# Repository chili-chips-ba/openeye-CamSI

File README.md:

# openEye-CamSI
Also see our [openEye-CamSI-Ethernet](https://github.com/chili-chips-ba/openeye-CamSI-ethernet) repo.

## Objective I

### Upgrade openCam Performance and Functionality
The goals of this development are to deliver complete video pipeline for three popular hi-rez imaging/camera sensors:
 - `2-lane RPiV2.1`, based on Sony IMX219, in `1280x720P@60Hz` RGB888 - `HD`
 - `4-lane OneInchEye`, based on Sony IMX283, in `1920x1080P@60Hz` RGB888 - `FHD`
 - `2-lane OV2740`, in a "Webcam" setup for Lukas Henkel's [openLaptop](https://resources.altium.com/p/open-source-laptop-part-one)

This is for mature, low-cost **Artix7 FPGAs**, by using its **IBUFDS, IDELAY, ISERDES** primitives in the camera front-end. These primitives are available in all IOBs, hence ubiquitous, relatively easy to work with, and already supported by opensource PNR for Xilinx Series7. This also allows future reduction of the total solution cost by migrating to [Spartan7](https://www.xilinx.com/video/fpga/spartan-7-technical-overview.html?_ga=2.252819658.271111311.1715447274-1421952438.1715447272), which does not have GTP transceivers (aka "true SerDes").

>To be clear -- We don't plan on using any of the 3rd party D-PHY front-end silicon devices specified in [XAPP894](https://github.com/chili-chips-ba/openeye-CamSI/blob/main/0.doc/Xilinx/MIPI/xapp894-d-phy-solutions.pdf). Moreover, we won't even use the passive signal conditioning networks that Xilinx is recommending. Instead, our objective is to achieve robust *Signal Integrity* (SI) and flawless HD/FHD video flow by pulling-in only on-chip resources.

This brings about multiple challenges. Compared to [StereoNinja's](https://github.com/StereoNinja/StereoNinjaFPGA) original work, which was for LatticeSemi ECP5 FPGA, our target device does not come with D-PHY receiver circuit *(no wonder why Artix7 costs less* :innocent:*)*.

On top of it, we are doing it on meager internal-to-FPGA BRAM budget, without expending much storage. In other words, PSRAM, SDRAM, DDR or similar external chips are NOT called to rescue. That's a major upgrade to StereoNinja's design, who realized end-to-end, camera-to-monitor streaming for only 640x480 VGA, and only in Grayscale, far below our vibrant RG888 color palette and HD/FHD quality. 

>This design is simpler and more affordable, hence uniquely appealing to the makers. It also paves a path to a cost-efficient openLaptop camera subsystem.

It is indeed the NLnet's objective for this project to bring StereoNinja's pioneering work to an order of magnitude higher performance and functionality level.

On the video feed sink side, we plan to showcase real-time streaming to:
 - **HDMI** monitor
 - **1Gbps Ethernet**, using UDP packets, rendered on a PC with [VLC Player](https://www.videolan.org)

The follow on "Webcam" project (aka Phase2) is to add **UVC** (USB2.0 Video Class) to this list. In prep for this future work, we plan to develop a number of add-on functions:
 - `Enable OV2740 camera chip`
 - `Image Signal Processing (ISP) 4 Webcam`
    > White Balance, Color Correction, Gamma Correction
 - `Video Compression 4 Webcam` - JPEG
    > Not needed for 1GE. But, compression is a must-have for the 1024P@30Hz over USB2

While our design is pushing Artix7 to its limits, it's these very silicon limits that stand in the way of getting more from the given imaging sensors. Recall that even StereoNinja's generally faster and better LatticeSemi FPGA cannot generate HDMI at 1920x1080@60Hz. 

Using Vivado tool chain, we were able to bring this design to the point where the only remaining factor preventing further resolution increase is the *Max Specified Toggle Rate* for Artix7 I/O structures and clock distribution networks.

## Objective II
### Add to opensource ecosystem 4 Xilinx

We are thrilled to use [openXC7](https://github.com/openXC7) toolkit, including its web-based CI/CD flow. That's both for the security of images taken, and to help openXC7 attain the level of robustness found in commercial / proprietary CAE tools, Xilinx Vivado in particular. In that sense, OpenEye-CamSI is the continuation of our [TetriSaraj](https://github.com/chili-chips-ba/openXC7-TetriSaraj), which was the first openXC7 test case for a design more complex than a mere blinky. 

>Our goal is to bring to the light issues that arrive from openXC7's first-ever exposure to demanding, cutting-edge designs like this one. 

It is important to note that, in its current state, openXC7 is rather immature, without even the basic timing awareness, yet alone timing-driven optimizations. It has never been used for designs that push the underlying silicon to the max. The as-is openXC7 is simply not adequate for proper timing closure.

While another project is underway and looking to plug this major opensource STA gap, it won't be ready for our Phase1. We're therefore planning Phase2 and Phase3, hoping to try this new timing closure prowess... Stress-testing, congesting, overwhelming it, all for the sake of making it more amenable to realizing higher Utilization and Fmax metrics with silicon at hand. 

The choice of our development platform was governed by the benefit for the greater community. The boards were selected for their opensource [CRUVI](https://github.com/micro-FPGA/CRUVI/blob/master/docs/CRUVI_Specification.pdf) connectivity spec. Yes, they are hardly used and don't come with support collateral found on the more popular hardware platforms. That's exactly why we opted for them!

We have indeed come across quite a few board problems and idiosyncrasies, spending a fair amount of time chasing issues that simply should not have been there. Still, since those are both opensource and EU products, this extra effort was for a good cause. We are certain that this project will help increase their visibility, and boost their acceptance rate among open makers. 

## Execution Play 1
### Laying a foundation
- [x] ✔ Familiarize with [Trenz](https://github.com/chili-chips-ba/openeye-CamSI/tree/main/0.doc/Trenz) hardware platform: Connectivity, clocking, power, etc. 
- [x] ✔ Bring up Blinky on Trenz
>___
- [x] ✔ Standalone HDMI image generation: 1280x720P@60Hz  RGB888 (HD)
- [x] ✔ Standalone HDMI image generation: 1920x1080P@30Hz RGB888 (FHD@30Hz)
- [x] ✔ Standalone HDMI image generation: 1920x1080P@60Hz RGB888 (FHD@60Hz). Established that FHD@60Hz is physically impossible with given silicon
>___
- [x] ✔ Experiments with IMX219 configuration and resolution options
- [x] ✔ Sniff Raspberry Pie interactions with Camera
- [x] ✔ Familiarize with *libcamera* drivers
>___  
- [x] ✔ Experiments with LVDS and termination schemes.
      How to do better than XAPP894, sharing insights with Lukas
>___
- [x] ✔ Test opensource [4-lane adapter](https://github.com/chili-chips-ba/openeye-CamSI/tree/main/0.doc/CRUVI-camera-adapter), sharing feedback with Edmund
- [x] ✔ Full redesign, fixing [bugs](https://github.com/chili-chips-ba/openeye-CamSI/blob/main/0.doc/CRUVI-camera-adapter/Technical-Note.TN-mipi.REV1.pdf) and expanding scope, to now include 2 and 4 lanes
>___
- [x] ✔ Clock Detection logic without standard LP I/O
- [x] ✔ SYNC Decoding logic and Byte Alignement
- [x] ✔ Word Alignement
- [x] ✔ Header Decoding and Stripping
- [x] ✔ Acquire static image from Camera, transfer it to DualPort BRAM, then HDMI
>___
- [x] ✔ Uncovered & debugged crosstalk problems on VHDPlus CRUVI adapter
- [x] ✔ Found Trenz [signal inversions and inconsistencies](https://github.com/chili-chips-ba/openeye-CamSI/blob/main/0.doc/CRUVI-camera-adapter/CRUVI-Pinout-4-and-2-lanes.xlsx), then shared with Antti
>___
- [x] ✔ HD video transfer from Camera to HDMI - At first jerky, with visible frame loss
- [x] ✔ Found CDC bug in opensource AsyncFIFO, sharing insights with IP owners
>___
- [x] ✔ Debayering logic for Color Space Conversion     
- [x] ✔ Synchronization logic for smooth video streaming, w/o external storage
>___

For this first play, the hardware was used in the following config:
- Trenz Carrier Card (TEB0707-02)
- Trenz 4x5 SoM with Artix-7 FPGA (TE0711-01)
- VHDPlus HDMI + 2-lane CSI Camera adapter
- Raspberry Pi V2.1 camera (Sony IMX219)

#### *Standalone HDMI image generation*
Our HDMI [image generator](https://github.com/chili-chips-ba/openeye-CamSI/tree/main/1.hw/lib/ip/hdmi) is limited by the toggle rate that's realistically possible with Artix7 clock and I/O primitives. The max we can get from it is:
- 720P@60Hz
- 1080P@30Hz
  
More about this and silicon limitations in [HDMI issue](https://github.com/chili-chips-ba/openeye-CamSI/issues/1#issue-2278453405). Here is the test image that our HDMI RTL outputs on its own, w/o camera connected to it:

#### *I2C for Camera Configuration*
There are many configurable registers in the IMX219 imaging sensor. Having fully familiarized with them, both by sniffing RPi I2C transactions and running own experiments, we've settled on the 720P@60Hz. I2C Controller was developped from the scratch, and used to load camera registers. More on it in [I2C issue](https://github.com/chili-chips-ba/openeye-CamSI/issues/3). 

Here is an illustration of I2C waveforms, i.e. our Control Plane protocol.

#### *Camera Connection*
Sony [IMX219](0.doc/Sensor.2-lane.RPi2.1/IMX219PQ.Datasheet.pdf) camera sensor is used for image acquisition. It is connected to FPGA with a 15-pin flex cable (FFC), using [VHDPlus](https://vhdplus.com/docs/components/camera) CRUVI module. We recommend checking our [blog](https://www.chili-chips.xyz/blog/untwisting-rpi5-camera-connectivity) for additional detail on this topic.

It turned out that the 4-lane CRUVI connector had a serious design flaw, essentially shorting system power. Having identified its root cause, we had to fully redesign it. We have also run into Trenz I2C wiring and supply complications related to onboard CPLD. Luckily, we managed to find a way around it without having to open the CPLD and change its internals.

#### *High-speed Signaling and Signal Integrity*
The VHDPlus CRUVI carries three 100 Ohm termination resistors, one for clock, plus two for data, as shown below: 

Location of these resistors close to data source is a major SI problem. Termination must be placed at the end of *Transmission Line* (TL), next to sink. Yet, on this system, the termination is not only misplaced, but there are also three connectors in the path of high speed signals:
- Camera to CRUVI -> `that's where the stock termination is placed`
- CRUVI to Carrier Card
- Carrier to FPGA SOM Card.

Consequently, we had to remove the stock termination and replace it with internal-to-FPGA resistors, so essentially relocating it to the very end of TL.

When Artix7 internal termination is used in connecton to LVDS_25 IOSTANDARD, it is important to set the correspoding bank's VCCIO to 2.5V. Only then will their differential resistance be 100 Ohms. 

That's on Trenz hardware done in the following way:
- switch DIP 2 to ON state, to set the IOV to 2.5V
- use Jumpers J14, J16, and J17 to connect VCCIO to IOV.
  
#### *Detection of Camera Clock Activity Intervals*
Once all these hardware and board problems were put behind, we turned focus back to RTL design. 

Given the goal to minimize overhead and eliminate the need for LP pins (see XAPP894), RTL had to provide a clever substitute for our non-existent I/O compared to standard Camera Serial Interface. After some experimentation, we settled on a scheme that detects blanking intervals between frames by using *Clock_Lock_FSM* with thresholds and timeouts. The output of this *Clock_Lock_FSM* is then used as global reset for the camera side of pipeline. That's to say that the video pipeline is out of reset only when camera clock is active and stable.

#### *CDC and Video Synchronization*
To have fluid and seamless video, we need to pass Pixel data with Line and Frame synchronization pulses from Camera to HDMI clock. Aiming for low-cost solution, this *Clock Domain Crossing* (CDC) and *Timebase Handoffs* are accomplished using Line Buffering instead of full Frame Buffering, so saving storage resources. More on this topic in [Line buffering issue](https://github.com/chili-chips-ba/openeye-CamSI/issues/2).

In addition to AsyncFIFO for **csi_clock->hdmi_clock** CDC, the signals that play crucial role in the *Timebase Handoffs* process are:
- csi_line_in
- hdmi_line_in

They mark the beginning of each new scan line in incoming video from Camera, as well as outgoing line to HDMI.

Furthermore, Async FIFO is kept in reset when either Camera or HDMI are Out-Of-Frame. It is through this **fifo_areset_n** and **hdmi_reset_n** that we are forcing HDMI to track the Camera. **rgb2hdmi** is the bridge between Camera and HDMI+GE worlds. Timing diagram below contains additional detail.

In all honesty, it took us a bit of trial-and-error to get it right. That was to some extent due to CDC bug we found in the fullness count of AsyncFIFO, which is the IP block we pulled from one of the opensource libraries. 

In the end, when everything was tuned, and AsyncFIFO CDC problem factored out of the solution, the final result came to be as nice and polished as follows:

#### *Clock and Block Diagram*

The following diagram illustrates design clocking scheme and block structure:

Design operates off of a single **external 100MHz** clock, from which we generate **200MHz refclk** for IDELAY and detection of camera activity. The camera clock comes in two forms:
- **CSI Bit** clock, for sampling and capturing incoming DDR data
- **CSI Byte** clock (= Bit clock / 4) for the rest of CSI video pipeline

The frequency of camera *Bit* and *Byte* clocks is the function of sensor resolution. A PLL on HDMI side generates two specific clocks from the common 100MHz input:
- **Parallel**, for RGB888 HDMI data
- **Serial**, (x5) for OSERDES and transmission of multiplexed video to monitor

The frequency of these two clocks is the function of HDMI resolution. We provide Verilog macros in the central *`top_pkg.sv`* for selection of HDMI resolution. 

The datapath is a straight video pipeline with option for width scaling via `NUM_LANE` parameter, which is also located in the central *top_pkg.sv*. 

The pipeline starts with circuits for capturing serial *Double Data Rate* (DDR) camera stream, eye-centering it using IDELAY, converting it to paralell format with ISERDES, then searching for *Byte boundaries*, followed by *Word alignement*, followed by *Packet Header* parsing and extraction of video *Payload* pixels.

It is only at this point, where video is *unpacked*, that we may engage in ISP. The ISP is a set of functions that could be as elaborate as one is willing to invest in them. Here is a [good read on it](https://www.eecs.yorku.ca/~mbrown/ICCV19_Tutorial_MSBrown.pdf). The extent of ISP for this project is clearly defined. The future Phase2 and Phase3 would add more. 

*Debayer* is the first ISP function we implemented. Without it, the displayed colors would have looked weird. More on it in [Debayer issue](https://github.com/chili-chips-ba/openeye-CamSI/issues/4).

## Execution Play 2
### Widening up the pathway
- [x] ✔ Repeat the same for the 4-lane IMX283 camera sensor
- [x] ✔ Step-by-step introduce the following 3 ISP elements:
  - [x] ✔ Debayer
  - [x] ✔ Dead Pixel Management
  - [x] ✔ Manual Exposure Control 
- [x] ✔ Implement another (lower) resolution of our choice

### *IMX283 Sensor Configuration for Different Resolutions*

Configuring the IMX283 sensor for different resolutions requires precise adjustment of its registers. For each data entry, the first four digits represent the register address, while the last two digits indicate the value to be written. Below, we describe the configuration process for achieving both **720p** and **1080p** resolutions at 60 FPS using **Mode 3** and **Mode 2**, respectively.

This sensor requires specific delays after setting some registers. In the [.mem](https://github.com/chili-chips-ba/openeye-CamSI/tree/main/1.hw/lib/ip/i2c_master) files, this is implemented as an additional byte appended to the three bytes representing the address and value of each register. These delays are crucial for ensuring proper operation and stability of the camera. More details can be found in our [issue](https://github.com/chili-chips-ba/openeye-CamSI/issues/29).

### **720p Resolution (60 FPS)**

For 720p resolution, **Mode 3** is used, which applies **3x3 horizontal/vertical binning**. This method combines pixel values within a 3x3 grid for each raw color channel, reducing resolution while maintaining image quality.

#### *Mode Settings*
The following registers enable **Mode 3** operation:
- `3004 1e`
- `3005 18`
- `3006 10`
- `3007 00`

#### *Frame Dimensions*
- **Y_OUT_SIZE**: Set the vertical size to 722 (0x2D2) to account for skipping 2 rows for debayer processing:
  - `302f d2`
  - `3030 02`
- **WRITE_VSIZE**: Set the vertical output size to 726 (0x2D6):
  - `3031 d6`
  - `3032 02`

#### *Frame Cropping*
- **H_TRIMMING_START**: Start the horizontal cropping at position 840 (0x348):
  - `3058 48`
  - `3059 03`
- **H_TRIMMING_END**: End the horizontal cropping at position 4584 (0x11E8):
  - `305a e8`
  - `305b 11`

These settings result in **1920 8-bit data points per line**, equivalent to **1280 12-bit raw data points** used for color processing.

#### *Timing Configuration for 60 FPS*
- **VMAX**: Set to 2551 (0x9F7) to ensure frame blanking:
  - `3038 f7`
  - `3039 09`
- **HMAX**: Set to 470 (0x1D6) to ensure line blanking:
  - `3036 d6`
  - `3037 01`

These settings ensure a frame rate of **60 FPS**.

### **1080p Resolution (60 FPS)**

For 1080p resolution, **Mode 2** is used, which applies **2x2 horizontal/vertical binning**. This method combines pixel values within a 2x2 grid for each raw color channel, maintaining higher resolution while reducing the overall pixel count.

#### *Mode Settings*
The following registers enable **Mode 2** operation:
- `3004 0d`
- `3005 11`
- `3006 50`
- `3007 00`

#### *Frame Dimensions*
- **Y_OUT_SIZE**: Set the vertical size to 1082 (0x43A):
  - `302f 3a`
  - `3030 04`

#### *Frame Cropping*
- **H_TRIMMING_START**: Start the horizontal cropping at position 840 (0x348):
  - `3058 48`
  - `3059 03`
- **H_TRIMMING_END**: End the horizontal cropping at position 4584 (0x11E8):
  - `305a e8`
  - `305b 11`

These settings result in **2880 8-bit data points per line**, equivalent to **1920 12-bit raw data points** used for color processing.

#### *Timing Configuration for 60 FPS*
- **VMAX**: Set to 2234 (0x8BA) to ensure frame blanking:
  - `3038 ba`
  - `3039 08`
- **HMAX**: Set to 540 (0x21C) to ensure line blanking:
  - `3036 1c`
  - `3037 02`

These settings ensure a frame rate of **60 FPS**.

### **Comparison of Configurations**

| Resolution | Mode   | Binning | Y_OUT_SIZE | VMAX   | HMAX | Frame Rate |
|------------|--------|---------|------------|--------|------|------------|
| 720p       | Mode 3 | 3x3     | 722        | 2551   | 470  | 60 FPS     |
| 1080p      | Mode 2 | 2x2     | 1082       | 2234   | 540  | 60 FPS     |

These configurations leverage the IMX283's advanced binning capabilities to optimize performance while maintaining high image quality.

You can watch a demonstration of this setup in action at the following link:

#### *Dead Pixel Management*

One of the key challenges in working with high-resolution sensors, like the IMX283, is managing dead pixels. These are defective pixels on the sensor that can negatively impact image quality. On this system, several strategies were implemented to effectively eliminate the impact of dead pixels.

#### *Resolution Constraints and the Use of Binning*

Due to the limitations of the Artix-7 FPGA, it is not possible to support the full resolution output of the IMX283 sensor. To address this, the resolution was reduced while still preserving image quality by utilizing all available pixels on the sensor. This was achieved through **binning**, a preprocessing step offered by the sensor itself.

- **For 720p Resolution**:  
  A **3x3 binning** method is used. From an 8x8 matrix of pixels, a 2x2 matrix is generated. This means that each new pixel is a combination of several neighboring pixels.
  
- **For 1080p Resolution**:  
  A **2x2 binning** method is used. From a 4x4 matrix of pixels, a 2x2 matrix is generated, combining adjacent pixels into one.

This process is illustrated in the image below:

By combining neighboring pixels, binning effectively acts as a form of filtering. This directly mitigates the effect of dead pixels, as their contribution is averaged out with surrounding pixel data.

#### *Debayering and Additional Averaging*

In addition to binning, the **debayering algorithm** implemented on this system further reduces the impact of dead pixels. The algorithm performs additional averaging across pixels to reconstruct color information. This further minimizes the possibility of dead pixels appearing in the final image.

#### *Manual Exposure Control*

Manual exposure control in the IMX283 sensor is achieved through the configuration of the `SVR` (Start Vertical Readout) and `SHR` (Start Horizontal Readout) registers. These registers determine the timing of the sensor's integration period, which is critical for controlling exposure and image brightness.

In our configuration we use:
1. **SVR = 0**: This value sets the integration start vertical period to the minimum possible value, effectively aligning the start of integration with the beginning of the readout period.
2. **SHR = 16**: This value specifies the integration start horizontal period. A higher `SHR` value reduces the integration time by shifting the horizontal readout window closer to the end of the frame.

By selecting these values, the integration time is minimized, which is suitable for scenarios with bright lighting conditions or high frame rate requirements.

## Execution Play 3 - Ethernet streaming
- [x] ✔ Add 1GE as second video sink, then move display to remote PC, via UDP VLC
- [x] ✔ Document implementation via block diagram and project repo

For additional detail, see our [openEye/CamSI-Ethernet](https://github.com/chili-chips-ba/openeye-CamSI-ethernet) repo.

## Execution Play 4 - Porting to openXC7
- [x] ✔ Create snap-free installation workflow
- [x] ✔ Port final design from Vivado to openXC7
- [x] ✔ Simulate it with Verilator and cocoTB, in CI/CD system  
- [x] ✔ Document scripts and flows used in this process

This task validates our Vivado-proven RTL with the openXC7 toolchain for Xilinx Series7 devices. The objectives are:
 - identify limitations in the opensource synthesis and PnR flow
 - document and analyze them
 - then collaborate with the openXC7 team to find the root causes and drive to resolutions.

#### openXC7 installation without Snap

A complete local installation method is provided for setting up the **openXC7 FPGA toolchain** without relying on Snap packages. This approach ensures full control over the environment and avoids Snap-related system constraints.

➡️ Full documentation: [Installation Guide](https://github.com/chili-chips-ba/openeye-CamSI/blob/main/3.build/openXC7/README.md)

#### Resolved Issues

Our extensive testing has resulted in uncovering a multitude of problems. They are fully documented and tracked in the relevant [openXC7 issues](https://github.com/chili-chips-ba/openeye-CamSI/issues?q=is%3Aissue%20label%3AopenXC7), along with specific testcase and solution we've arrived to with openXC7 developers.

#### Remaining Challenge: OSERDES10 Support

One significant limitation remains: openXC7 currently supports only single OSERDES configurations with maximum 8-to-1 muxing ratio. Our design requires 10-to-1 serialization using Master-Slave OSERDES setup (two cascaded OSERDES), which is yet to be supported. As the openXC7 team continues working on this advanced use case, our [Issue42](https://github.com/chili-chips-ba/openeye-CamSI/issues/42) remains open for tracking purposes.

#### Bonus Deliverable: SoftOSERDES10 workaround for Issue42

Looking to temporarily alleviate OSERDES10 limitation, as an unsolicited/bonus contribution to the project we've developed a plug-and-play compatible _SoftOSERDES10 module_. For it, we use a 10-bit latch with a 5-bitpair shift register, followed by an ODDR primitive (which is supported by openXC7). 

Key takeaways from our approach:
- **Clock domains**: Parallel clock (`clk_par`) for data loading; Serial clock (`clk_ser`, 5x faster) for shifting
- **Edge detection**: Captures parallel data on `clk_par` rising edge using edge detection logic
- **Shift operation**: Right-shift by 2 bits per cycle, sending the LSB first to ODDR primitive
- **DDR output**: The ODDR primitive outputs one bit on each clock edge (`shift_reg[0]` on rising, `shift_reg[1]` on falling)

Our implementation follows the same **LSB-first serialization** as Xilinx OSERDESE2, where bit 0 of the parallel data is transmitted first, followed by bit 1, bit 2, and so on. Along with pinout compatibility, that also ensures behavioral plug-and-play with OSERDES primitive, but implemented mostly in CLBs. Naturally, the Fmax of our hybrid CLB + ODDR approach will not be on par with the true hardware OSERDES.

Detailed timing and block diagrams illustrate this soft, CLB-based approach.

## Execution Play 5.1 - Prepping for Webcam (by Chili.CHIPS*ba team)

- [x] ✔ Enable OV2740 camera chip: 
   - [x] ✔ Bring up Lukas' new adapter board
   - [x] ✔ Reverse-engineer I2C settings
   - [x] ✔ Demonstrate CAM-to-HDMI video path

#### *OV2740 Sensor Configuration for the 720p resolution*

Configuring the OV2740 sensor for 720p resolution requires precise adjustment of its registers. Each data entry comprises a six-digit code: the first four digits specify the register address, while the final two digits denote the value to be written.

The first step is to configure the sensor's output type. For this setup, the 8-bit mode was selected by writing the value 0x08 to the register 0x3031, as shown below:

- `3031 08`

Although the camera outputs RAW 10-bit data, the ISP block processes the data and enables an 8-bit RAW output at the interface.

A crucial step in setting up the OV2740 sensor is configuring the PLL to generate two essential clocks:

MIPI PHY Clock: This clock is critical for the MIPI interface and must match the clock frequency on the FPGA side to ensure proper communication.

SCLK (System Clock): This clock is used by the Image Sensor Processor (ISP) block. It is vital to set the frequency high enough; otherwise, the ISP block will not have sufficient time to complete all its tasks, potentially leading to image processing errors.

The correct clock frequencies are ensured by configuring the following registers.

- **MIPI PHY**: 450 MHz
- `0302 4b`
- `030a 01`
  
- **SCLK**:   
- `030d 4b`
- `030e 01`
- `0312 11`

#### *720p resolution*
- **H_OUTPUT_SIZE**: Set the horizontal size to 1280 (0x500): 
- `3808 05`
- `3809 00`
- **V_OUTPUT_SIZE**: Set the vertical size to 720 (0x2d0): 
- `3801 02`
- `380b d0`

The next step is configuring the frame rate to 60 FPS. This is achieved by setting two key registers: HTS (Horizontal Timing Size) and VTS (Vertical Timing Size). Understanding how these registers affect the camera's data (signals) is essential for proper configuration.

HTS (Horizontal Timing Size):
Increasing the value of HTS extends the duration of sending a complete line, including both the useful data and the blanking period. However, it is crucial to maintain the duty cycle of the entire frame while adjusting HTS, as this directly impacts the frame rate.

VTS (Vertical Timing Size):
Increasing the value of VTS extends the duration of sending the entire frame, including the blanking period. By adjusting VTS, you control the total frame time, which also influences the resulting frame rate.

The duration of a line or frame does not depend on the number of pixels per line or per frame, but only on the values of HTS and VTS.

- **HTS**: Set the HTS to 1816 (0x718): 
- `380c 07`
- `380d 18`
- **VTS**: Set the VTS to 1000 (0x3e8): 
- `380e 03`
- `380f e8`

A demonstration of this configuration is provided below, using a test image generated by the camera.

<div align="center">
  
</div>

## Execution Play 5.2 - Prepping for Webcam (by Silicon Highway Technologies webcam team)

- [x] ✔ Add 3 new ISP functions
   - [x] ✔ White Balance
   - [x] ✔ Color Correction
   - [x] ✔ Gamma Correction
- [x] ✔ JPEG video compression

The goal of this part of the project was to implement and test (1) a **color balancing IP block** and (2) a **JPEG image compression IP block**, both to be parts of an image or video pipeline. 

- (1) was based on https://www.ipol.im/pub/art/2011/llmps-scb/?utm_source=doi which is a color balance algorithm performing ***white balance*, *color correction* and *gamma correction* simultaneously**. The **Simple Color Balance (SCB)** block was thus implemented from scratch and tested first using behavioural simulations in *Verilator* and *Vivado* and subsequently using post-PNR simulations in the *Vivado Simulation Environment* for the target device.

- (2) is based on an IP implemented by Robert Metchev in Verilog RTL: https://github.com/brilliantlabsAR/frame-codebase/tree/main/source/fpga/modules/camera/jpeg_encoder. The provided *JPEG* block was tested using behavioural simulation with *Cocotb*.

### **Simple Color Balance (SCB)**
**SCB** IP Block available software code was available from https://www.ipol.im/pub/art/2011/llmps-scb/?utm_source=doi. 

A hardware implementation must work with “live” images, however, i.e. groups of pixels per frame, flowing through an image pipeline. The hardware implementation of the *SCB* thus works on a frame by frame basis, correcting the colours of frame `n` in frame `(n + 1)`. The gap between frames is sufficient to compute the colour balance frame ratios, i.e. 
`frameratio = 255/(max RGB – min RGB)` per RGB channel, using dividers. Then, colours are balanced “live”, during frame `(n + 1`), by multiplying the input pixel colour `i` by `(i – min) x frameratio`.

The pixel clock frequency of `36MHz` is sufficient to perform multiplications “live”, as pixels come in and go out through the SCB IP Block. This was checked using post-PNR simulations in Vivado as both timing was closed for the design and entire images were validated to be balanced correctly.

In the following two figures, the effect of the *SCB* algorithm can be seen. On the left is the original image, which appears to be faded out, and on the right is the balanced image, which appears brighter and livelier, due to the color balancing:

<p align="left">
  
&nbsp; &nbsp; &nbsp; &nbsp;
  
</p>

Similarly, a sequence of frames that represents a video, can be displayed in the following figures. The range of the RGB values changes from frame to frame, and the *SCB* algorithm tries to balance them, based on each previous frame.
- Input Frames:

- Output Frames:

In the screenshot below, the processing of one of the frame lines is shown. Previously, one identical frame has already been loaded, to configure the min-max ranges. In the input frame, all RGB values are within the range `[64, 196]`, so the SCB algorithm translates them to the range `[0, 255]`, with minor precision inaccuracies that do not have a large visible impact. The balancing is performed using multipliers which have a single cycle delay, thus this algorithm converts each frame with a single-cycle delay.

### **JPEG**
The *JPEG* design was tested on `1280x720` images, initially on one single frame, and afterwards on multiple frames, simulating a video. Each frame is successfully converted from a bitmap image to a converted image in the *JPEG* format. To add the required headers, in order to display each *JPEG* image, external python functions are used.

This specific *JPEG* module requires three clocks of different frequencies: the pixel clock, which always runs at `36MHz`, a *JPEG* slow clock and a *JPEG* fast clock. The slow clock can run at `12MHz`, `18MHz`, `24MHz` or `36MHz`, while the fast clock must be at least twice as fast as the slow clock.

The *JPEG* module can take four discrete **Quality Factor (QF)** values as input. These are `10%`, `25%`, `50%` and `100%`. The functionality of the design was verified for each of these values, with visual differences being observed.

Below, two compressed images with different *QF* are displayed. The left image has a `10%` *QF* and the right has a `50%` *QF*:

To model the three clocks, we use an **MMCM** (Mixed Mode Clock Manager) to generate them from the `100MHz` clock of the board. For the slow clock, we choose a frequency of `12MHz`, and for the fast clock, we choose a frequency of `72MHz`.

In the simulation screenshot below, two frames are processed and a compressed output file is produced for each one. The signal image_valid_out rises when a compressed image is ready. The *JPEG* data words are sampled from the output signal data_out.

---
## Trenz and CRUVI in retrospect

The hardware platform originally selected for this project proved to be a capital miss and source of most of our troubles. 

We ended up having to debug board and connectivity issues on PCBAs that no one used before, or combinations thereof that the manufacturer never tested. Be it incorrect termination resistors, straight shorts, cold solder joints and opens on flaky connectors, signal integrity degradation from too much modularity / discontinuity on the path, swaps of differential pairs, or wiring high-speed clocks to the non-Clock Capable (CC) FPGA pins, the share of board issues we had to deal with was overwhelming.

On top of that comes scarce availability of Trenz board, with lead times in excess of three months for a simple passive CRUVI Debug Card. All that has cost us dearly in time and effort. Yes, CRUVI is open-source. Yes, Trenz is European. But, we cannot afford to keep investing and loosing so much in order to support that cause.

Going forward, we are parting away with Trenz CRUVI system, and switching to Puzhitech [PA-StarLite](https://www.aliexpress.us/item/3256806434967523.html?gps-id=pcStoreJustForYou&scm=1007.23125.137358.0&scm_id=1007.23125.137358.0&scm-url=1007.23125.137358.0&pvid=c1d02f3c-8f66-4b76-a24a-a72144960d79&_t=gps-id%3ApcStoreJustForYou%2Cscm-url%3A1007.23125.137358.0%2Cpvid%3Ac1d02f3c-8f66-4b76-a24a-a72144960d79%2Ctpp_buckets%3A668%232846%238107%231934&pdp_npi=4%40dis%21USD%21128.44%21102.75%21%21%21901.32%21721.06%21%402101c67a17281960440137763ec377%2112000037845115402%21rec%21US%212013047485%21XZ&spm=a2g0o.store_pc_home.smartJustForYou_2010082555490.1005006621282275&gatewayAdapt=glo2usa). This compact card brings everything we need for video projects off-the-bat, within basic package, including 2-lane MIPI CSI connector, HDMI output and 1Gbps Ethernet. No need for multiple add-on cards and connectors to put together a useable system that's 3x more expensive, more fragile, and not in stock.

This card also comes with solid expension potential via two 40-pin standard 100mil headers. They are mechanically robust, physically accessible for debugging, and still can carry relatively high-speed signals thanks to short, balanced wiring on the mainboard.

While [Puzhitech](http://www.puzhitech.com/en) board already comes with 15-pin 0.5mm FPC for 2-lane MIPI CSI, the 40-pin 100mil headers can be used to hook up additional RPi cameras via its [15-pin 1mm](https://tinkersphere.com/cables-wires/3843-15-pin-05mm-1mm-pitch-fpc-to-dip-breakout.html#/soldered_side-1mm) FPC, as well as 22-pin 0.5mm connector for the 4-lane interface. Below is a picture of the [adapters](https://www.ebay.com/itm/175795228114?mkcid=16&mkevt=1&mkrid=711-127632-2357-0&ssspo=1cGlwdPqS5y&sssrc=4429486&ssuid=QKddZKcUTzu&var=475196039437&widget_ver=artemis&media=MORE) we used. We recommend fitting them with DIP connectors that have longer legs, so that they protrude on the bottom side, and also serve as attachment points for oscilloscope. That alleviates the need for the €36 Trenz Debug Connector and its impossibly long lead time of 3+ months.

# Phase2 - USB Webcam
- See: https://nlnet.nl/project/FPGA-ISP-UVM-USB2 (2024-02-099)

# Phase3 - openCam/Event

This project aims to introduce the field of Event Cameras to open-source domain. It does it by developing the following three outcomes:
  1) interface to an entry-level Prophesee/Sony event imaging sensor, and its integration with PC systems
  2) novel algorithms for processing event-based video data
  3) efficient FPGA-based hardware acceleration platform for these algorithms.

The interface will enable physical connectivity, configuration, and live data transfer via Ethernet. The algorithm development will decode and interpret event video frames, extracting key features such as rapid motion events. The acceleration track will port these algorithms to an FPGA embedded system that implements a soft processor customized for video workloads, programmable in high-level languages, blending hardware and software methods for high throughput and efficiency.

Together, these three outcomes will create the first fully open-source platform for exploring and utilizing Event Camera technology, paving the way for future applications.

All these elements are new, not only for the open-source community, but also the professional industry.

The project goal is to form a solid base from which the makers can start developing open-source apps with Event Camera. It is in that sense similar to uberDDR3. The scope of this initial project will include a couple of Getting Started examples, such as recording the mechanical vibrations of an industrial motor, or inside a high-voltage switch, or counting the free-falling beans.

There are many other possible applications of this technology. They span industrial, medical, automotive, IOT, VR, mobile, high-speed photography, aerospace, and beyond. New applications and use-cases are also constantly invented. We intend to exploit some of them in the subsequent project proposals.

Just for background, here are a few references to what can be done with this technology:
- https://inivation.com/solutions
- https://www.prophesee.ai/event-based-vision-industrial
- https://www.prophesee.ai/event-based-vision-automotive
- https://www.prophesee.ai/event-based-vision-medical
- https://www.prophesee.ai/event-based-vision-xr
- https://www.prophesee.ai/event-based-vision-mobile
- https://www.prophesee.ai/event-based-vision-iot
- https://www.prophesee.ai/event-based-vision-more-applications
  
The primary objective of this project is to open the door for open-source developers to enter this vast and mostly unexplored application space.

## Public Announcements
  [2026/05/02](https://www.linkedin.com/posts/chili-chips_fpga-share-7456476683760480256-Ay5s?utm_source=share&utm_medium=member_desktop&rcm=ACoAAAJv-TcBSi_5ff0VNMrInrT-xg44YF3jnyU)
  
  [2024/12/14](https://www.linkedin.com/posts/chili-chips_sony-imx283-camera-1080p-60fps-stream-with-activity-7273936850312916992-ZF01?utm_source=share&utm_medium=member_desktop)

## *Acknowledgements*
We are grateful to:
 - NLnet Foundation's sponsorship for giving us an opportunity to work on this fresh new take at FPGA video processing.
 - StereoNinja, whose project has set the stage for this major upgrade of opensource camera performance and functionality, as well as its expansion from LatticeSemi to Xilinx ecosystem.

This project was funded through the NGI0 Entrust Fund, a fund established by NLnet with financial support from the European Commission's Next Generation Internet programme, under the aegis of DG Communications Networks, Content and Technology under grant agreement No 101069594.

#### End of Document

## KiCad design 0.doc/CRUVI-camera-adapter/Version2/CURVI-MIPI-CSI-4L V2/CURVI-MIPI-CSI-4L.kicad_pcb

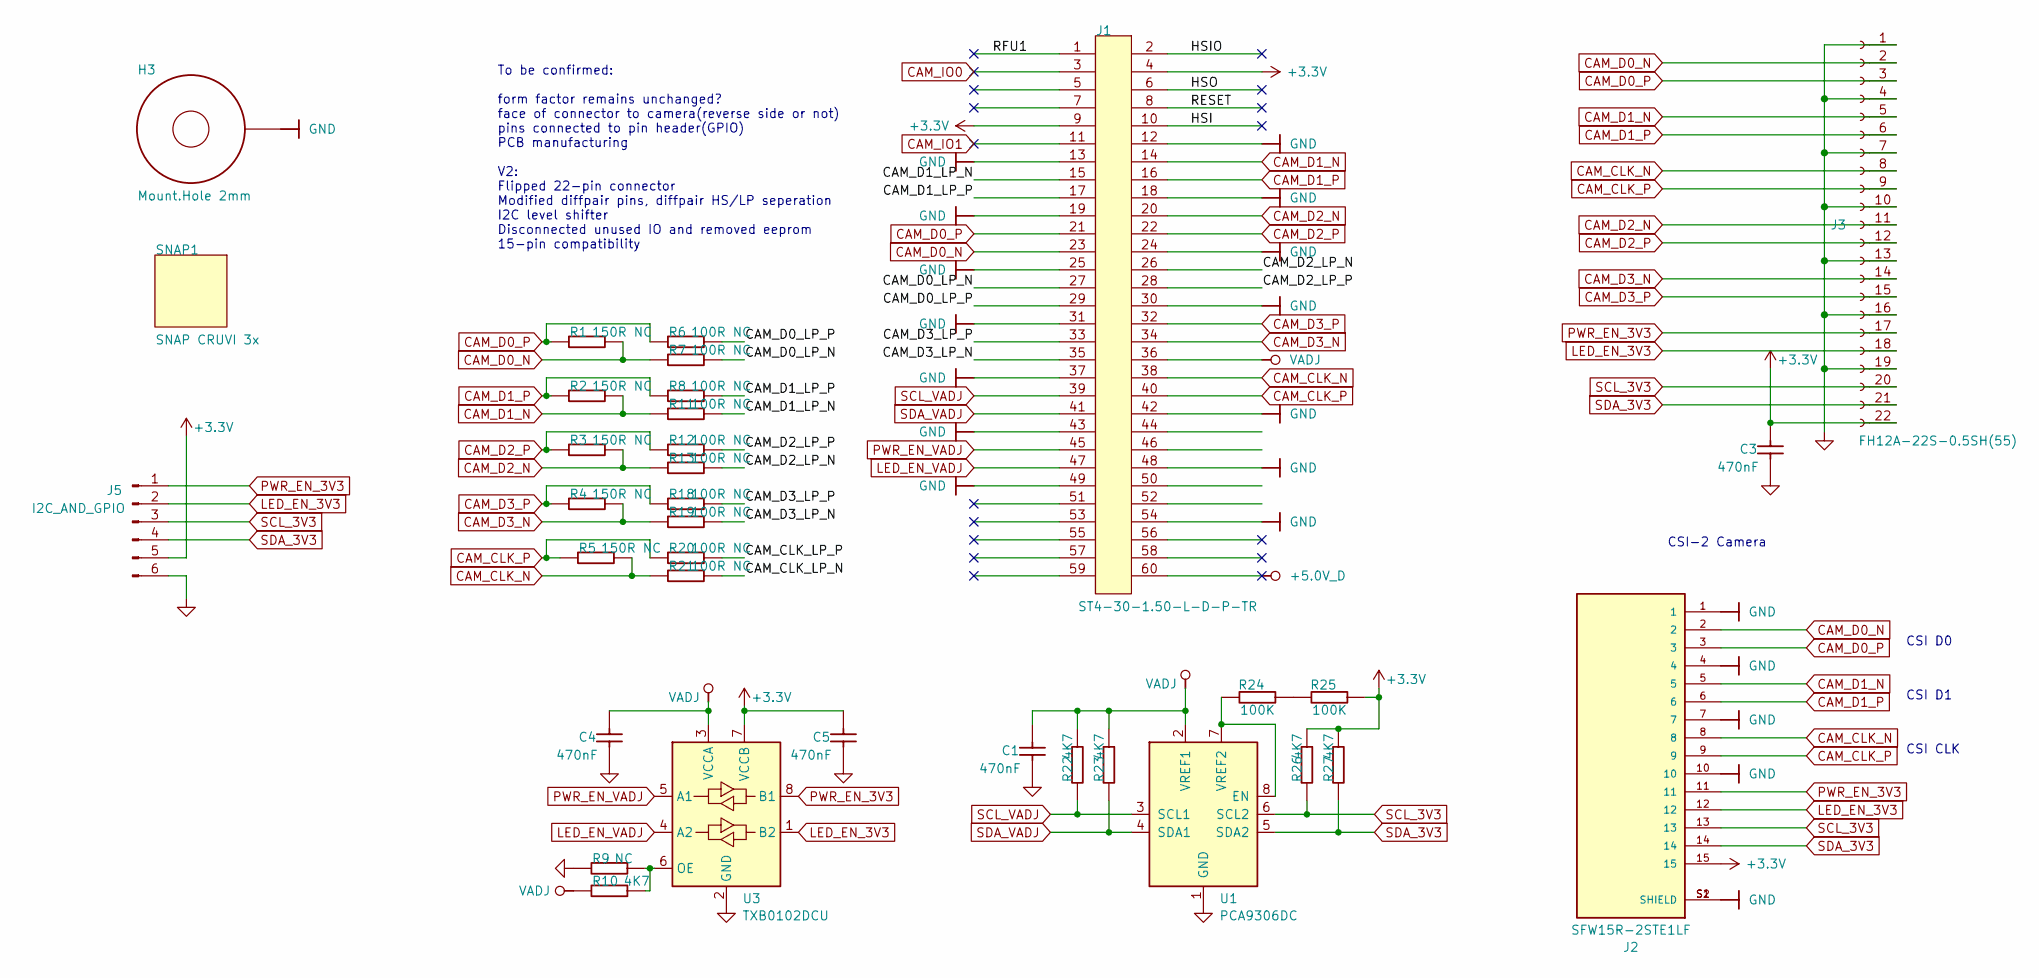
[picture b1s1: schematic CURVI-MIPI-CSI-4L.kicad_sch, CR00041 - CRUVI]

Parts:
C1, C3, C4, C5: 470nF; C_0402_1005Metric; VOLTAGE 6.3V; TOLERANCE 20%
H3: Mount.Hole 2mm; MHole2_2mm
J1: ST4-30-1.50-L-D-P-TR; CURVI_HIGHSPEED_ST4-30-1_50-L-D
J2: SFW15R-2STE1LF; AMPHENOL_SFW15R-2STE1LF; PARTREV AE
J3: FH12A-22S-0.5SH(55); Hirose_FH12-22S-0.5SH_1x22-1MP_P0.50mm_Horizontal; Part Description 22 Position FFC, FPC Connector Contacts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
J5: I2C_AND_GPIO; PinHeader_1x06_P1.27mm_Vertical
R1, R2, R3, R4, R5: 150R NC; R_0402_1005Metric; TOLERANCE 1%
R6, R7, R8, R11, R12, R13, R18, R19, R20, R21: 100R NC; R_0402_1005Metric; TOLERANCE 1%
R9: NC; R_0402_1005Metric; TOLERANCE 1%
R10, R22, R23, R26, R27: 4K7; R_0402_1005Metric; TOLERANCE 1%
R24, R25: 100K; R_0402_1005Metric; TOLERANCE 1%
SNAP1: SNAP CRUVI 3x; CRUVI_3x_Snap
U1: PCA9306DC; VSSOP-8_2.3x2mm_P0.5mm
U3: TXB0102DCU; VSSOP-8_2.4x2.1mm_P0.5mm

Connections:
+3V3: C3.1, C5.1, J1.4, J1.9, J2.15, J3.22, J5.5, R25.2, R26.2, R27.2, U3.7 (VCCB)
+5.0V_D: J1.60
/CAM_CLK_LP_N: R21.2
/CAM_CLK_LP_P: R20.2
/CAM_D0_LP_N: J1.27, R7.2
/CAM_D0_LP_P: J1.29, R6.2
/CAM_D1_LP_N: J1.15, R11.2
/CAM_D1_LP_P: J1.17, R8.2
/CAM_D2_LP_N: J1.26, R13.2
/CAM_D2_LP_P: J1.28, R12.2
/CAM_D3_LP_N: J1.35, R19.2
/CAM_D3_LP_P: J1.33, R18.2
/HSI: J1.10
/HSIO: J1.2
/HSO: J1.6
/RESET: J1.8
/RFU1: J1.1
CAM_CLK_N: J1.38, J2.8, J3.8, R5.2, R21.1
CAM_CLK_P: J1.40, J2.9, J3.9, R5.1, R20.1
CAM_D0_N: J1.23, J2.2, J3.2, R1.2, R7.1
CAM_D0_P: J1.21, J2.3, J3.3, R1.1, R6.1
CAM_D1_N: J1.14, J2.5, J3.5, R2.2, R11.1
CAM_D1_P: J1.16, J2.6, J3.6, R2.1, R8.1
CAM_D2_N: J1.20, J3.11, R3.2, R13.1
CAM_D2_P: J1.22, J3.12, R3.1, R12.1
CAM_D3_N: J1.34, J3.14, R4.2, R19.1
CAM_D3_P: J1.32, J3.15, R4.1, R18.1
CAM_IO0: J1.3
CAM_IO1: J1.11
GND: C1.2, C3.2, C4.2, C5.2, H3.1, J1.12, J1.13, J1.18, J1.19, J1.24, J1.25, J1.30, J1.31, J1.37, J1.42, J1.43, J1.48, J1.49, J1.54, J2.1, J2.4, J2.7, J2.10, J2.S1 (SHIELD), J2.S2 (SHIELD), J3.1, J3.4, J3.7, J3.10, J3.13, J3.16, J3.19, J5.6, R9.1, U1.1 (GND), U3.2 (GND)
LED_EN_3V3: J2.12, J3.18, J5.2, U3.1 (B2)
LED_EN_VADJ: J1.47, U3.4 (A2)
unnamed: R24.2, R25.1
unnamed: R24.1, U1.7 (VREF2), U1.8 (EN)
unnamed: R9.2, R10.2, U3.6 (OE)
PWR_EN_3V3: J2.11, J3.17, J5.1, U3.8 (B1)
PWR_EN_VADJ: J1.45, U3.5 (A1)
SCL_3V3: J2.13, J3.20, J5.3, R26.1, U1.6 (SCL2)
SCL_VADJ: J1.39, R22.1, U1.3 (SCL1)
SDA_3V3: J2.14, J3.21, J5.4, R27.1, U1.5 (SDA2)
SDA_VADJ: J1.41, R23.1, U1.4 (SDA1)
VADJ: C1.1, C4.1, J1.36, R10.1, R22.2, R23.2, U1.2 (VREF1), U3.3 (VCCA)

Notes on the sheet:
To be confirmed: form factor remains unchanged? face of connector to camera(reverse side or not) pins connected to pin header(GPIO) PCB manufacturing V2: Flipped 22-pin connector Modified diffpair pins, diffpair HS/LP seperation I2C level shifter Disconnected unused IO and removed eeprom 15-pin com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
CSI D1
CSI-2 Camera
CSI CLK
CSI D0

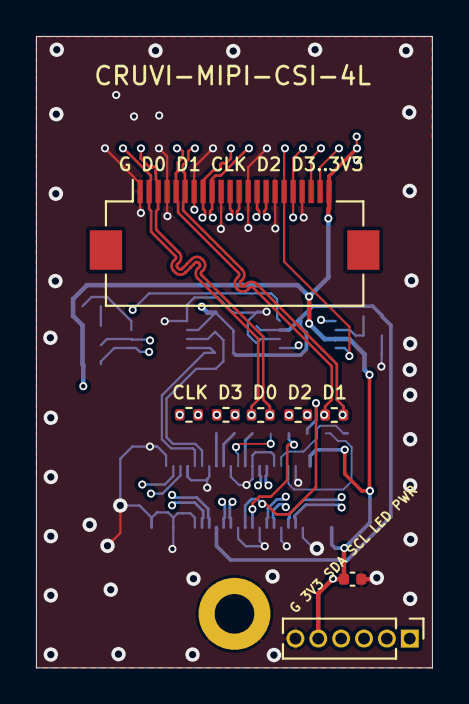
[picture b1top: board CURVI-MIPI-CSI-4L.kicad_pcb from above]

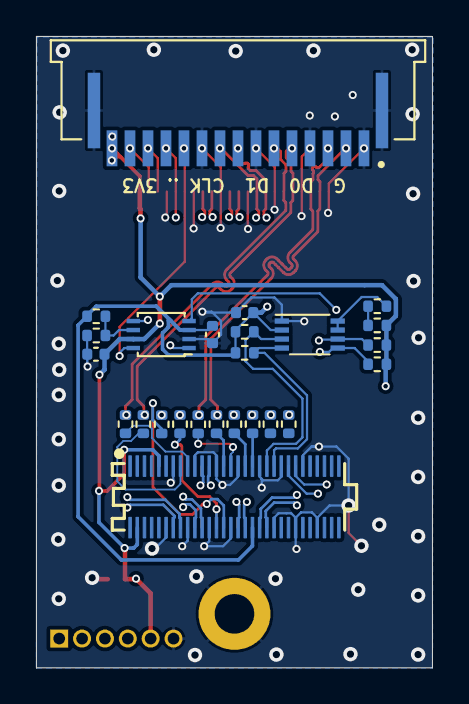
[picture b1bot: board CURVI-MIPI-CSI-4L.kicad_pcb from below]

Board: 4 copper layers, 22.0 x 35.1 mm, 34 parts (25 on the bottom side), 32 nets.

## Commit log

2023-12-12 Initial population
2023-12-25 added schematic of the 4-lane CRUVI CSI extension board
2023-12-31 Documentation for the camera sensor
2024-01-04 added GTP and GTH/GTX SerDes docs
2024-01-04 renamed
2024-01-06 change top names
2024-01-09 added 1GE PHY docs
2024-01-11 added reference to ISP doc
2024-01-16 initial seed
2024-01-18 Added HDMI SV modules and constraints file
2024-01-19 added CSI2 model
2024-01-19 added block diagram
2024-02-06 unpacked xapp894
2024-02-10 Added info on IDELAY component
2024-02-22 added references for UDP
2024-03-06 Added CPLD info
2024-03-12 added 4-lane CRUVI pinout
2024-03-12 added Connectivity diagram for 2-lane-VHDPlus CRUVI camera adapter
2024-03-14 CSI_RX initial draft
2024-03-23 added Bank power info to XLS
2024-03-23 Added power-related CRUVI info.
2024-03-23 added OneInch camera module schematic
2024-03-27 added VHDPlus schematics
2024-03-28 added Version2 of the 4-lane CRUVI
2024-04-03 added V2 info
2024-04-05 updated 4-lane CRUVI board design
2024-04-11 added info on the VHDPlus CRUVI correlated XTalk
2024-05-03 Readme update.
2024-05-03 Added Images
2024-05-03 Add image
2024-05-05 Remove images
2024-05-06 Initial population of RTL for WP1
2024-05-06 WP1 update
2024-05-07 Added sim model of Xilinx primitives
2024-05-07 added FPGA Block Diagram seed
2024-05-09 Revert "Merge branch 'main' of https://github.com/chili-chips-ba/openeye-CamSI"
    This reverts commit 1a92faf7030b13eab5c30c7310456b21671c9e08, reversing
    changes made to 657a951d3454d34c943693463d57e4ad72990d8b.
2024-05-09 Revert "initial population"
    This reverts commit 657a951d3454d34c943693463d57e4ad72990d8b.
2024-05-11 updated Block Diagram
2024-05-11 added reference to OV2740 "Webcam" sensor to the Block Diagram
2024-05-12 re-organize
2024-05-12 initial stubs
2024-05-12 fix paths
2024-05-12 Added .gitattributes
2024-05-12 Changed .gitattributes
2024-05-12 1. Cocotb infrastructure 2. models dir: Add only the absolute minimum of modules (xSERDES: only stubs for now) 3. Code changes to support Cocotb+Icarus+Verilator compilation 4. minor bug fix
2024-05-12 use simple sim model for SERDES
2024-05-12 undo delete
2024-05-12 clean up
2024-05-12 added Timing Diagram
2024-05-13 testbench to simulate Xilinx models
2024-05-13 BUFR parameter mus be string
2024-05-13 specify mem file from command line
2024-05-13 PLL models
2024-05-13 change generate block _lane to lane, otherwise verilator wont capture
2024-05-13 ISERDES sim model
2024-05-15 further streamlined design structure and updated Vivado build setup
2024-05-15 constraints update
2024-05-15 bug update
2024-05-15 Read verilog sources from 1.hw/top.filelist
2024-05-15 add dependency on source files
2024-05-15 add Readme
2024-05-15 fix typo
2024-05-15 more Icarus clean up
2024-05-15 minor
2024-05-15 add SIM_ONLY
2024-05-16 1. add RUN_TIME_US Makefile variable 2. use cocotbext.i2c package
2024-05-16 define SDA & SCL as tri1 for Cocotb purposes
2024-05-16 make sure I2C gets correctly reset at power up
2024-05-16 Use the standard method to drive SDA and SCL using IOBUF.
2024-05-17 a round of updates related to synth and sim issues
2024-06-01 i2c_reset changed
2024-06-03 Fixed I2C reset first issue
2024-06-04 Minor clean up
2024-06-04 I2C Testbench: cocotbext-i2c & Icarus
2024-06-06 More i2c_top improvements
2024-06-06 added OV2640 adapter card pictures
2024-06-10 added SCH and User Manual for the Webcam CRUVI adapter
2024-06-11 Basic functions for cam_dphy_data/clk
2024-06-13 Added comment
2024-06-13 Long packet sim problem
2024-06-13 Added .gtkw for csi-2 and i2c
2024-06-27 creating LICENSES directory
2024-06-27 adding headers with copyright and license info to various files
2024-06-29 Successfully tested functions with the Verilator
2024-06-29 Added and tested (on 2 lanes) CSI class
2024-06-29 Skip IDELAYE2 primitive for now (Verilator)
2024-06-30 Ecc successfully tested
2024-07-04 Successfully tested entire code in Verilator
2024-07-06 added camera optics photo
2024-07-08 Pulled csi_rx_align_word.sv from main
2024-07-09 Fixed and tested packet_handler for 4 lanes
2024-07-11 added Webcam optics detail
2024-07-13 Fixed and tested raw2rgb.sv for 4 lanes
2024-07-15 Create LICENSE
2024-07-17 a round of linting
2024-07-18 Added initial hooks for MIPI_1_LANE support. WIP
2024-07-19 optimized 'align_word' for area by removing one pipeline stage
2024-07-19 added License info
2024-08-03 Added raw10 support and 4-lane simulation
2024-09-04 Enabled only writing logic "0" on IO port, and adapted IO port names to FSM and logic i2c_ctrl.sv module
    The names of the IN / OUT ports are adapted to the logic of the i2c_ctrl.sv module. Two new OUT ports scl_oe and sda_oe have been created, which put the I/O into high-impedance 3-state mode when
    I/O is used for read (input) operation. In the write operation these signals set logic "0" on the I/O port, and leave the I/O port in 3-state when it write logic "1". In this way, avoids the collisio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
2024-09-12 Added support for raw12 data, sim and hw
2024-09-14 Added CR0200 demo
2024-10-14 added Puzhitech card
2024-10-17 Docs for CRUVI debug board
2024-10-23 added new Puzhitech picture
2024-10-23 added 0.5mm FPC to 100mil adapter picture
2024-10-23 updated logo
2024-10-29 Updated i2c part according to issue
2024-10-29 Changed names of .mem files
2024-10-31 added PuzhiTech schematic
2024-11-03 PuZhi examples
2024-11-06 openXC7 design
2024-11-06 openXC7 design - update
2024-11-07 Adjusted IMX283 .mem file
2024-11-10 added Lint setup
2024-11-10 Full HD res with 30fps on imx283 registar set
2024-11-12 Updated i2c part. Fully parameterized
2024-11-12 Updated vivado project and constraint file
2024-11-12 Updated for code readability
2024-11-12 Adjusted HDMI configuration for 1080p res at 30Hz
2024-11-12 Refined clock detection for clocks near 200MHz from 4-lane sensor
2024-11-25 Adjusted clock generation
2024-11-25 Added some new debug pins
2024-11-25 Adjusted raw2rgb module for 4-lane sensor with 12bits
2024-11-25 Changed camera and hdmi sync
2024-11-26 Updated de-Bayer filter logic, switch from RGGB to GBRG pattern
2024-11-26 Added some comments and headers
2024-11-26 IMX283 register set for 1080p 60 fps
2024-11-27 Successfully tested 4-lane sensor with 1080p 60fps
2024-11-27 Changed name of .mem file for 4-lane senzor for 720p 60fps
2024-11-27 Added set of registers for OV2740 sensor
2024-11-27 Updated vivado project
2024-11-28 Updated constrait files, added parts for 2-lane sensors
2024-11-30 Corrected isp_top module
2024-12-01 Update vivado project
2024-12-01 Add BUFR instead of BUFMR
2024-12-04 Init ethernet files
    Committed all ethernet core files needed for UDP stream. Added new config values ETHERNET and PUZHI.
2024-12-05 Constraints with ethernet for Trenz and Puzhi
    Added constraints files with included ethernet pins for Trenz and Puzhi boards
2024-12-05 Docs for CRUVI Ethernet boards
2024-12-10 added debug waveforms
2024-12-11 added power up sequence waveforms
2024-12-12 Update sim part, add readme
2024-12-15 block diagram update
2024-12-18 Added files for the simple color balance ISP algorithm
2024-12-18 updated license
2024-12-19 added SI example
2024-12-19 new data points
2024-12-19 Add pwd for ov2740
2024-12-20 more webcam debug datapoints
2024-12-22 Update i2c_ctrl.sv
    Fixed "rump pulse" issue on the clock signal at beginning communication i2c
2025-01-04 added new test images
2025-01-07 added new test image, now with good sync
2025-01-13 Updated reset synchronizer for simple color balance
2025-01-16 Update README.md with ISP info
2025-01-20 Created JPEG folder
2025-01-20 Added JPEG files
2025-01-20 Update README.md with JPEG info
2025-01-21 2lane rpi debug
2025-01-23 Small changes
2025-01-23 Added parts for the webcam - OV2740
2025-01-24 added headers
2025-01-26 added hex sticker artwork
2025-01-29 Bug fixed
2025-01-29 openXC7 - project update
2025-01-30 Add clock dedicated route
2025-02-06 Video player for custom UDP Streamer
    The initial code for a video player (VP). We created two independent application, one is in C++ on the Qt framework and second using Python. The C++ VP uses the opencv library while the Python script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
2025-02-08 Makefile: Added target dependencies for error1 & error2
2025-02-19 Update Makefile
2025-03-02 update cs_rx_clk_det.v for Issue40
2025-03-23 Code cleaning
    Cleaning the code from unused methods.
2025-04-24 Remove submodule csi-ethernet files from main repository
    Created new submodule for ethernet (csi-ethernet). In this submodule, new Vivado project csi_eth.xdc created. All ethernet related files from main repository moved to this submodule, also these files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
2025-04-24 Update submodule csi-ethernet
2025-04-24 Create clocks 125 MHz for ethernet
2025-04-24 Added config parameters for HDMI2VGA
    HDMI2VGA is config variable for platform where use adapter HDMI to VGA
2025-04-24 Fixed REFCLK_FREQUENCY and set IBUFDS to Highest Performance
2025-04-24 Set IBUFDS Highest Performance and clear unused code
2025-04-24 Assign rgb_out for PUZHI board
2025-04-24 Added clocks 125MHz for Ethernet and update logic for input clock
    Input clock can be 100Mhz in case Trenz board or 200MHz for Puzhi board.
2025-04-24 Switched places with HDMI channels 0 and 2
    Switched places HDMI channels to have correct RGB colors. Issue on the design of the HDMI test board.
2025-04-24 Deleted ethernet pins from main Trenz repository
2025-04-24 Added logic for HDMI2VGA config variable
    Define the HDMI2VGA variable when using a physical HDMI to VGA adapter
2025-04-24 Separate logic for generating hdmi_reset_n when use OV2740 and other sensors
2025-06-12 Added constraints for Artix7-100 Puzhi
2025-06-17 Moved Puzhi constraints to ethernet submodule
2025-06-17 Update csi-ethernet
2025-11-13 Added openxc7 scripts
2025-12-14 Add script to update Yosys version (0.60)
2026-05-02 added more artwork
